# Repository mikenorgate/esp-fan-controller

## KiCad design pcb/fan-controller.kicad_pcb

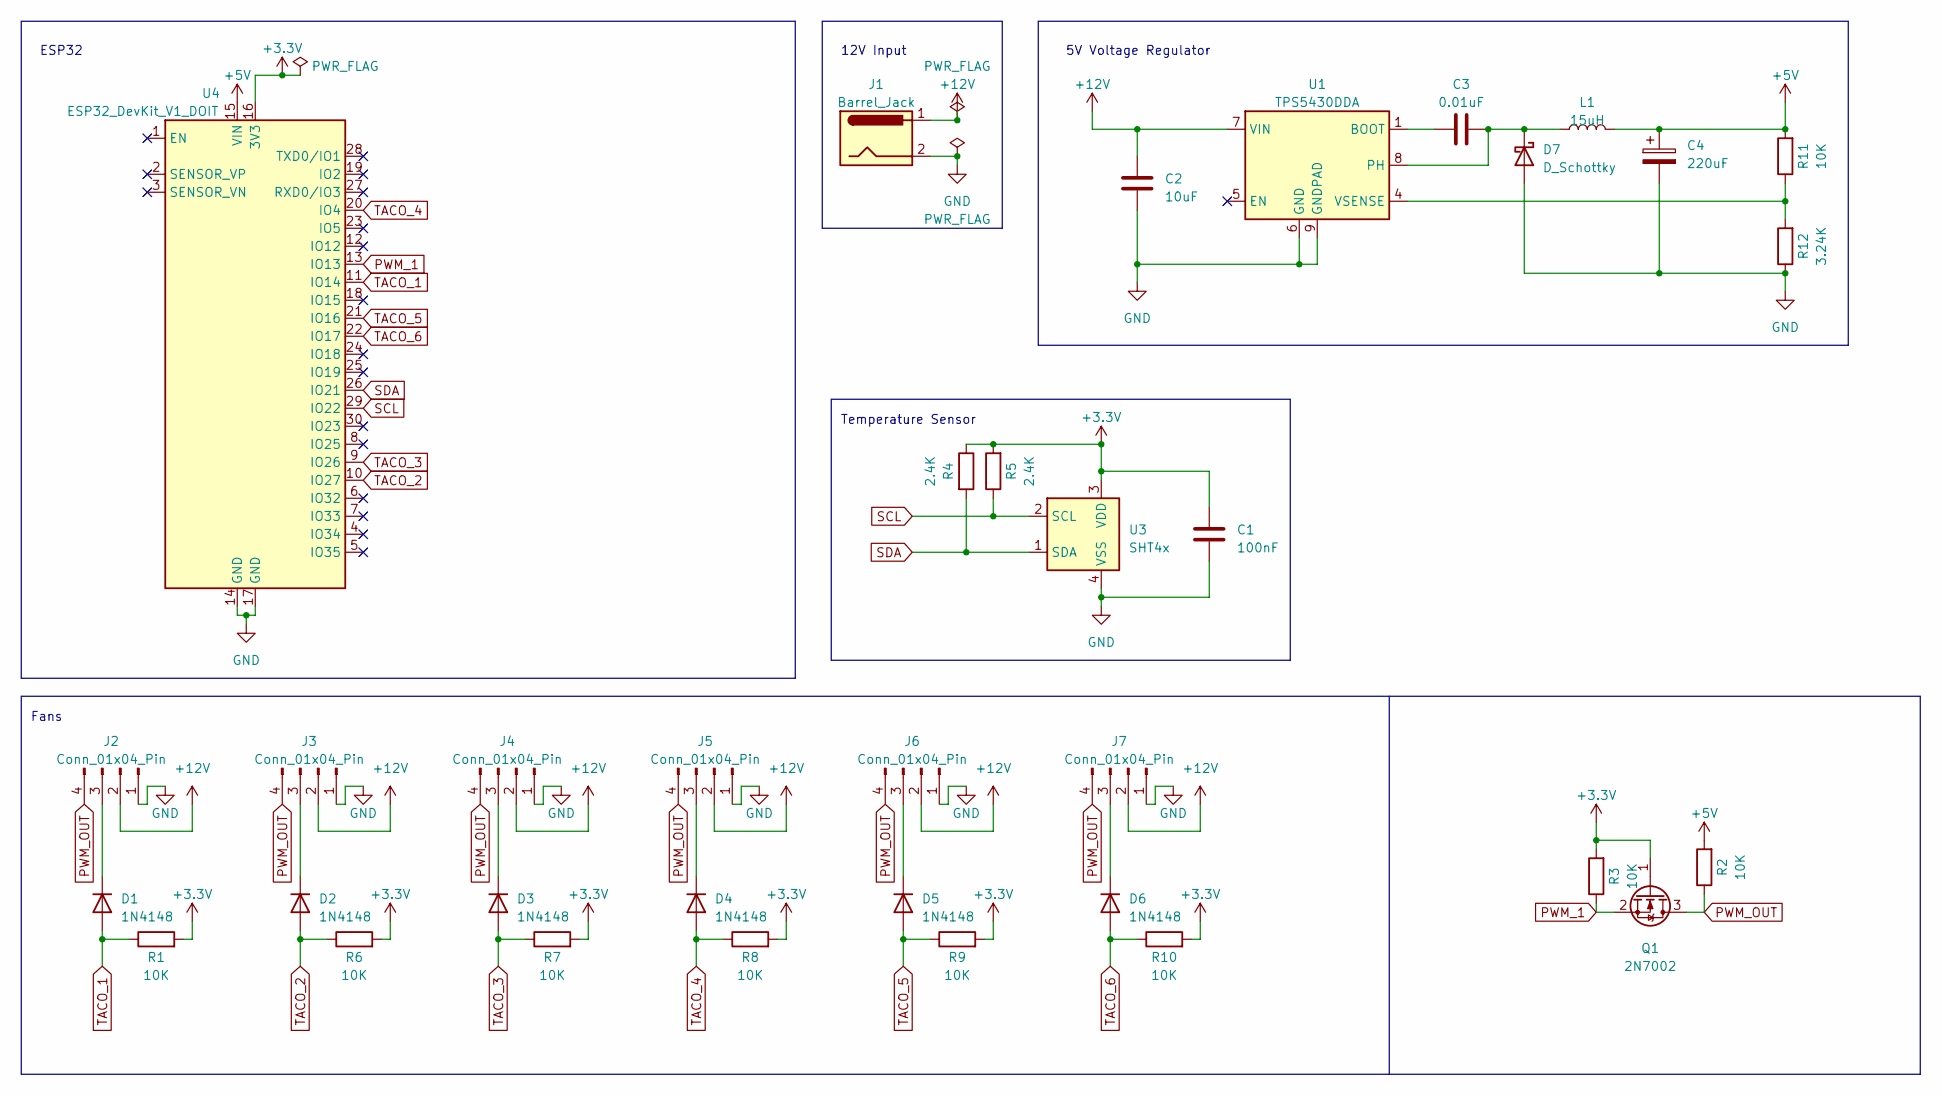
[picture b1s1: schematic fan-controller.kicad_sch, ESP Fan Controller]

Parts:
C1: 100nF; C_0603_1608Metric
C2: 10uF; C_0603_1608Metric
C3: 0.01uF; C_0603_1608Metric
C4: 220uF; CP_EIA-3528-12_Kemet-T
D1, D2, D3, D4, D5, D6: 1N4148; D_SOD-123
D7: D_Schottky; D_SOD-123
J1: Barrel_Jack; BarrelJack_Horizontal
J2, J3, J4, J5, J6, J7: Conn_01x04_Pin; Molex_KK-254_AE-6410-04A_1x04_P2.54mm_Vertical
L1: 15uH; L_1210_3225Metric
Q1: 2N7002; SOT-23
R1, R2, R3, R6, R7, R8, R9, R10, R11: 10K; R_0603_1608Metric
R4, R5: 2.4K; R_0603_1608Metric
R12: 3.24K; R_0603_1608Metric
U1: TPS5430DDA; TI_SO-PowerPAD-8_ThermalVias
U3: SHT4x; Sensirion_DFN-4_1.5x1.5mm_P0.8mm_SHT4x_NoCentralPad
U4: ESP32_DevKit_V1_DOIT; esp32_devkit_v1_doit

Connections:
+3.3V: C1.1, Q1.1 (G), R1.2, R3.2, R4.1, R5.2, R6.2, R7.2, R8.2, R9.2, R10.2, U3.3 (VDD), U4.16 (3V3)
+5V: C4.1, L1.2, R2.2, R11.2, U4.15 (VIN)
+12V: C2.1, J1.1, J2.2, J3.2, J4.2, J5.2, J6.2, J7.2, U1.7 (VIN)
GND: C1.2, C2.2, C4.2, D7.2 (A), J1.2, J2.1, J3.1, J4.1, J5.1, J6.1, J7.1, R12.1, U1.6 (GND), U1.9 (GNDPAD), U3.4 (VSS), U4.14 (GND), U4.17 (GND)
unnamed: D1.1 (K), J2.3
unnamed: D2.1 (K), J3.3
unnamed: D3.1 (K), J4.3
unnamed: D4.1 (K), J5.3
unnamed: D5.1 (K), J6.3
unnamed: D6.1 (K), J7.3
unnamed: C3.2, D7.1 (K), L1.1, U1.8 (PH)
unnamed: C3.1, U1.1 (BOOT)
unnamed: R11.1, R12.2, U1.4 (VSENSE)
PWM_1: Q1.2 (S), R3.1, U4.13 (IO13)
PWM_OUT: J2.4, J3.4, J4.4, J5.4, J6.4, J7.4, Q1.3 (D), R2.1
SCL: R5.1, U3.2 (SCL), U4.29 (IO22)
SDA: R4.2, U3.1 (SDA), U4.26 (IO21)
TACO_1: D1.2 (A), R1.1, U4.11 (IO14)
TACO_2: D2.2 (A), R6.1, U4.10 (IO27)
TACO_3: D3.2 (A), R7.1, U4.9 (IO26)
TACO_4: D4.2 (A), R8.1, U4.20 (IO4)
TACO_5: D5.2 (A), R9.1, U4.21 (IO16)
TACO_6: D6.2 (A), R10.1, U4.22 (IO17)

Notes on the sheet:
5V Voltage Regulator
Fans
ESP32
12V Input
Temperature Sensor

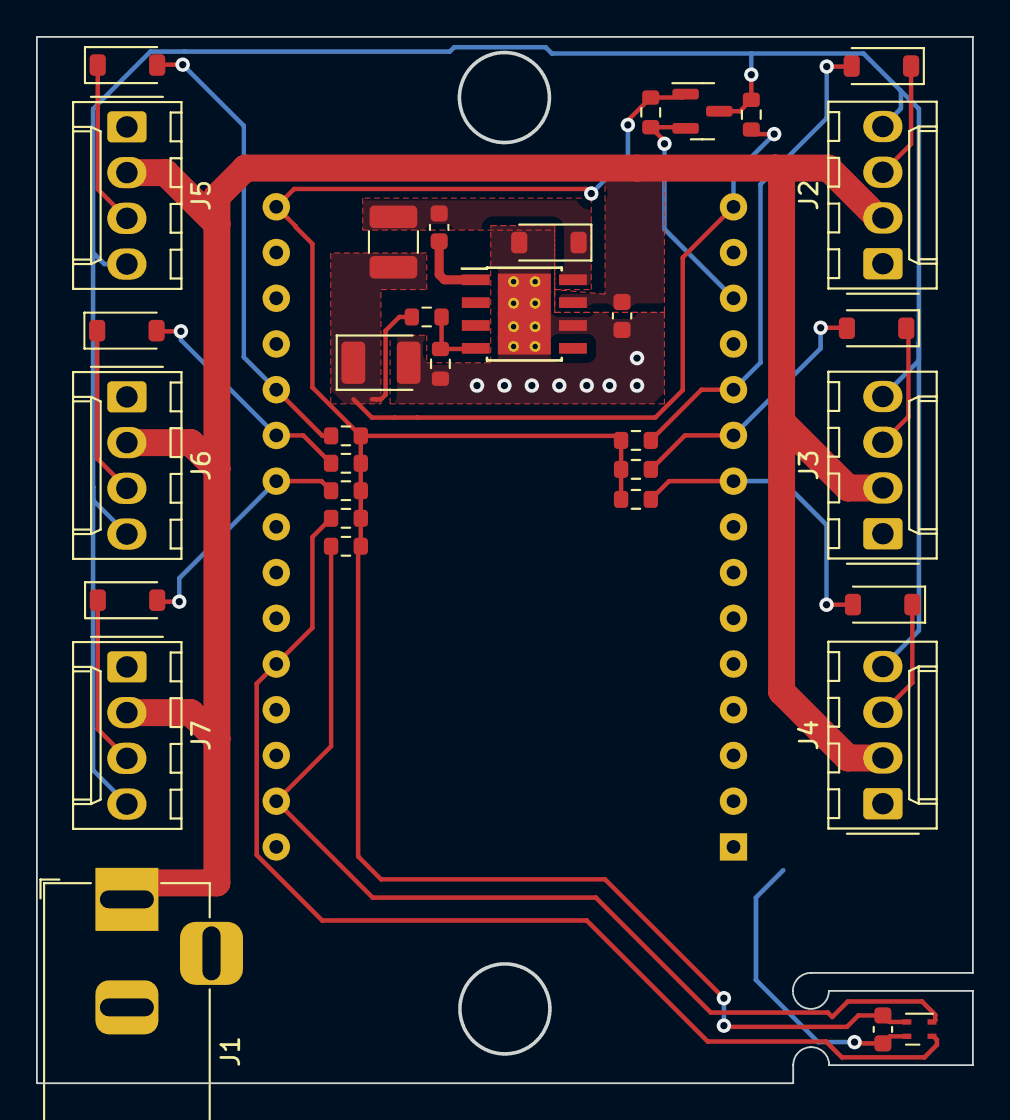
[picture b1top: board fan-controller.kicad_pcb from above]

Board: 2 copper layers, 51.9 x 58.0 mm, 35 parts (0 on the bottom side), 23 nets.

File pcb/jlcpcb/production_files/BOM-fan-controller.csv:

Comment,Designator,Footprint,LCSC
100nF,C1,C_0603_1608Metric,C14663
2.4K,"R4,R5",R_0603_1608Metric,C22940
3.24K,R12,R_0603_1608Metric,C22994
D_Schottky,D7,D_SOD-123,C2480
10K,"R1,R10,R11,R2,R3,R6,R7,R8,R9",R_0603_1608Metric,C25804
220uF,C4,CP_EIA-3528-12_Kemet-T,C2887903
SHT4x,U3,Sensirion_DFN-4_1.5x1.5mm_P0.8mm_SHT4x_NoCentralPad,C2909890
15uH,L1,L_1210_3225Metric,C478845
0.01uF,C3,C_0603_1608Metric,C57112
1N4148,"D1,D2,D3,D4,D5,D6",D_SOD-123,C81598
2N7002,Q1,SOT-23,C8545
10uF,C2,C_0603_1608Metric,C96446
TPS5430DDA,U1,TI_SO-PowerPAD-8_ThermalVias,C9864
Conn_01x04_Pin,J6,Molex_KK-254_AE-6410-04A_1x04_P2.54mm_Vertical,
Conn_01x04_Pin,J4,Molex_KK-254_AE-6410-04A_1x04_P2.54mm_Vertical,
Barrel_Jack,J1,BarrelJack_Horizontal,
Conn_01x04_Pin,J5,Molex_KK-254_AE-6410-04A_1x04_P2.54mm_Vertical,
Conn_01x04_Pin,J2,Molex_KK-254_AE-6410-04A_1x04_P2.54mm_Vertical,
Conn_01x04_Pin,J3,Molex_KK-254_AE-6410-04A_1x04_P2.54mm_Vertical,
Conn_01x04_Pin,J7,Molex_KK-254_AE-6410-04A_1x04_P2.54mm_Vertical,
ESP32_DevKit_V1_DOIT,U4,esp32_devkit_v1_doit,

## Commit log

2023-04-24 Initial PCB design
2023-05-06 change voltage regulation
